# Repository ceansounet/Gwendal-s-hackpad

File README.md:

# Gwendal-s-hackpad
My personnal Hackpad

## PCB
here is the schematic of my pcb :

and here is the resulting layout, it needs to be pretty compact to fit in the 100mm*100mm requirements

The silkscreen was made on figma and imported as an SVG. (sources are [here](pcb/assets))

## BONUS
Since I had extra space and the kit comes with them, I figured I could include the rotary encoders inside a bonus version of my hackpad, while the main version keeps only 16 inputs to fit within the limit

## BOM:
Here should be everything you need to make this hackpad

in the kit :
- 16x Cherry MX Switches
- 16x DSA Keycaps
- 2x M3x5x4 Heatset inserts
- 2X M3x12mm SHCS Bolts
- 16x 1N4148 DO-35 Diodes
- 1x 0.91" 128x32 OLED Display
- 1x XIAO RP2040
- 1x Case (3 printed parts)

to source yourself :
- 1x MCP23017 (I²C IO expander)
- 1x 100nF Capacitor (decoupling the MCP power)
- 8x 4.7k ohm resistors (pull up/pull down resistors for the matrix and the I²C circuit)

Optional :
- 2x EC11 Rotary Encoder
- 2x 1N4148 DO-35 Diodes
- 1x 8cm² cork sheet (for the bottom of the case)

## EXTRA STUFF :
I designed this project in 4 days of vacation, learnt to use kicad and pcb design in general
If firmware doesn't support 2 different I²C circuits, I added 0 ohm resistors (R9 and R10), that can be soldered shut to make a single I²C circuit, currently it uses 2 by default for speed and stability.
I designed the case to be 3d printable without supports (exept the cutout bit on the top cover, purely for aesthetic purposes, feel free to fill it in to avoid supports entirely).
I made some firmware that should support the matrix, but does not support the encoders nor the OLED screen yet, I am waiting until I have actually made the board to test it.

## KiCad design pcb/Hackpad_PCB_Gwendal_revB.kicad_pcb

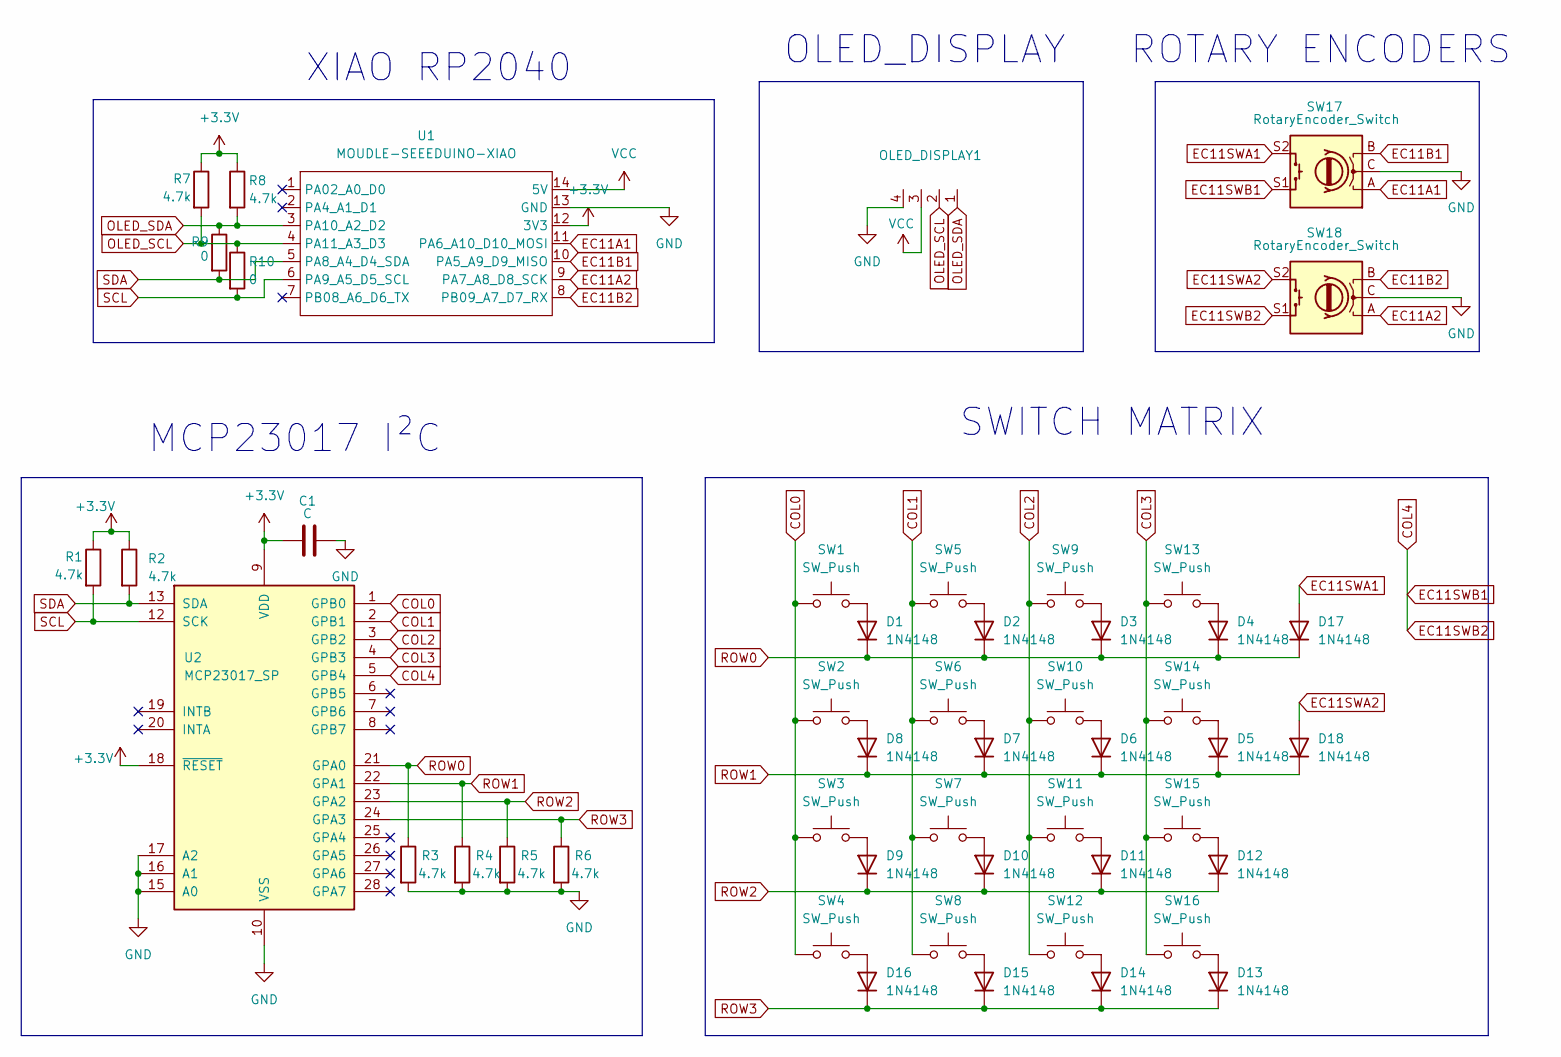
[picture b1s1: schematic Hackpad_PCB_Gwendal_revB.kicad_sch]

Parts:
C1: C; C_Disc_D5.0mm_W2.5mm_P5.00mm
D1, D2, D3, D4, D5, D6, D7, D8, D9, D10, D11, D12, D13, D14, D15, D16, D17, D18: 1N4148; D_DO-35_SOD27_P7.62mm_Horizontal
OLED_DISPLAY1: PinHeader_1x04_P2.54mm_Vertical
R1, R2, R3, R4, R5, R6, R7, R8: 4.7k; R_Axial_DIN0207_L6.3mm_D2.5mm_P7.62mm_Horizontal
R9, R10: 0; R_Axial_DIN0207_L6.3mm_D2.5mm_P7.62mm_Horizontal
SW1, SW2, SW3, SW4, SW5, SW6, SW7, SW8, SW9, SW10, SW11, SW12, SW13, SW14, SW15, SW16: SW_Push; SW_Cherry_MX_1.00u_PCB
SW17, SW18: RotaryEncoder_Switch; RotaryEncoder_Alps_EC11E-Switch_Vertical_H20mm
U1: MOUDLE-SEEEDUINO-XIAO; XIAO-Generic-Hybrid-14P-2.54-21X17.8MM
U2: MCP23017_SP; DIP-28_W7.62mm

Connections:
+3.3V: C1.1, R1.1, R2.1, R7.1, R8.1, U1.12 (3V3), U2.9 (VDD), U2.18 (~RESET)
COL0: SW1.1, SW2.1, SW3.1, SW4.1, U2.1 (GPB0)
COL1: SW5.1, SW6.1, SW7.1, SW8.1, U2.2 (GPB1)
COL2: SW9.1, SW10.1, SW11.1, SW12.1, U2.3 (GPB2)
COL3: SW13.1, SW14.1, SW15.1, SW16.1, U2.4 (GPB3)
COL4: SW17.S1, SW18.S1, U2.5 (GPB4)
EC11A1: SW17.A, U1.11 (PA6_A10_D10_MOSI)
EC11A2: SW18.A, U1.9 (PA7_A8_D8_SCK)
EC11B1: SW17.B, U1.10 (PA5_A9_D9_MISO)
EC11B2: SW18.B, U1.8 (PB09_A7_D7_RX)
EC11SWA1: D17.2 (A), SW17.S2
EC11SWA2: D18.2 (A), SW18.S2
GND: C1.2, OLED_DISPLAY1.4, R3.2, R4.2, R5.2, R6.2, SW17.C, SW18.C, U1.13 (GND), U2.10 (VSS), U2.15 (A0), U2.16 (A1), U2.17 (A2)
unnamed: D1.2 (A), SW1.2
unnamed: D2.2 (A), SW5.2
unnamed: D3.2 (A), SW9.2
unnamed: D4.2 (A), SW13.2
unnamed: D5.2 (A), SW14.2
unnamed: D6.2 (A), SW10.2
unnamed: D7.2 (A), SW6.2
unnamed: D8.2 (A), SW2.2
unnamed: D9.2 (A), SW3.2
unnamed: D10.2 (A), SW7.2
unnamed: D11.2 (A), SW11.2
unnamed: D12.2 (A), SW15.2
unnamed: D13.2 (A), SW16.2
unnamed: D14.2 (A), SW12.2
unnamed: D15.2 (A), SW8.2
unnamed: D16.2 (A), SW4.2
OLED_SCL: OLED_DISPLAY1.2, R7.2, R10.1, U1.4 (PA11_A3_D3)
OLED_SDA: OLED_DISPLAY1.1, R8.2, R9.1, U1.3 (PA10_A2_D2)
ROW0: D1.1 (K), D2.1 (K), D3.1 (K), D4.1 (K), D17.1 (K), R3.1, U2.21 (GPA0)
ROW1: D5.1 (K), D6.1 (K), D7.1 (K), D8.1 (K), D18.1 (K), R4.1, U2.22 (GPA1)
ROW2: D9.1 (K), D10.1 (K), D11.1 (K), D12.1 (K), R5.1, U2.23 (GPA2)
ROW3: D13.1 (K), D14.1 (K), D15.1 (K), D16.1 (K), R6.1, U2.24 (GPA3)
SCL: R1.2, R10.2, U1.6 (PA9_A5_D5_SCL), U2.12 (SCK)
SDA: R2.2, R9.2, U1.5 (PA8_A4_D4_SDA), U2.13 (SDA)
VCC: OLED_DISPLAY1.3, U1.14 (5V)

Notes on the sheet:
XIAO RP2040
MCP23017 I²C
ROTARY ENCODERS
OLED_DISPLAY
SWITCH MATRIX

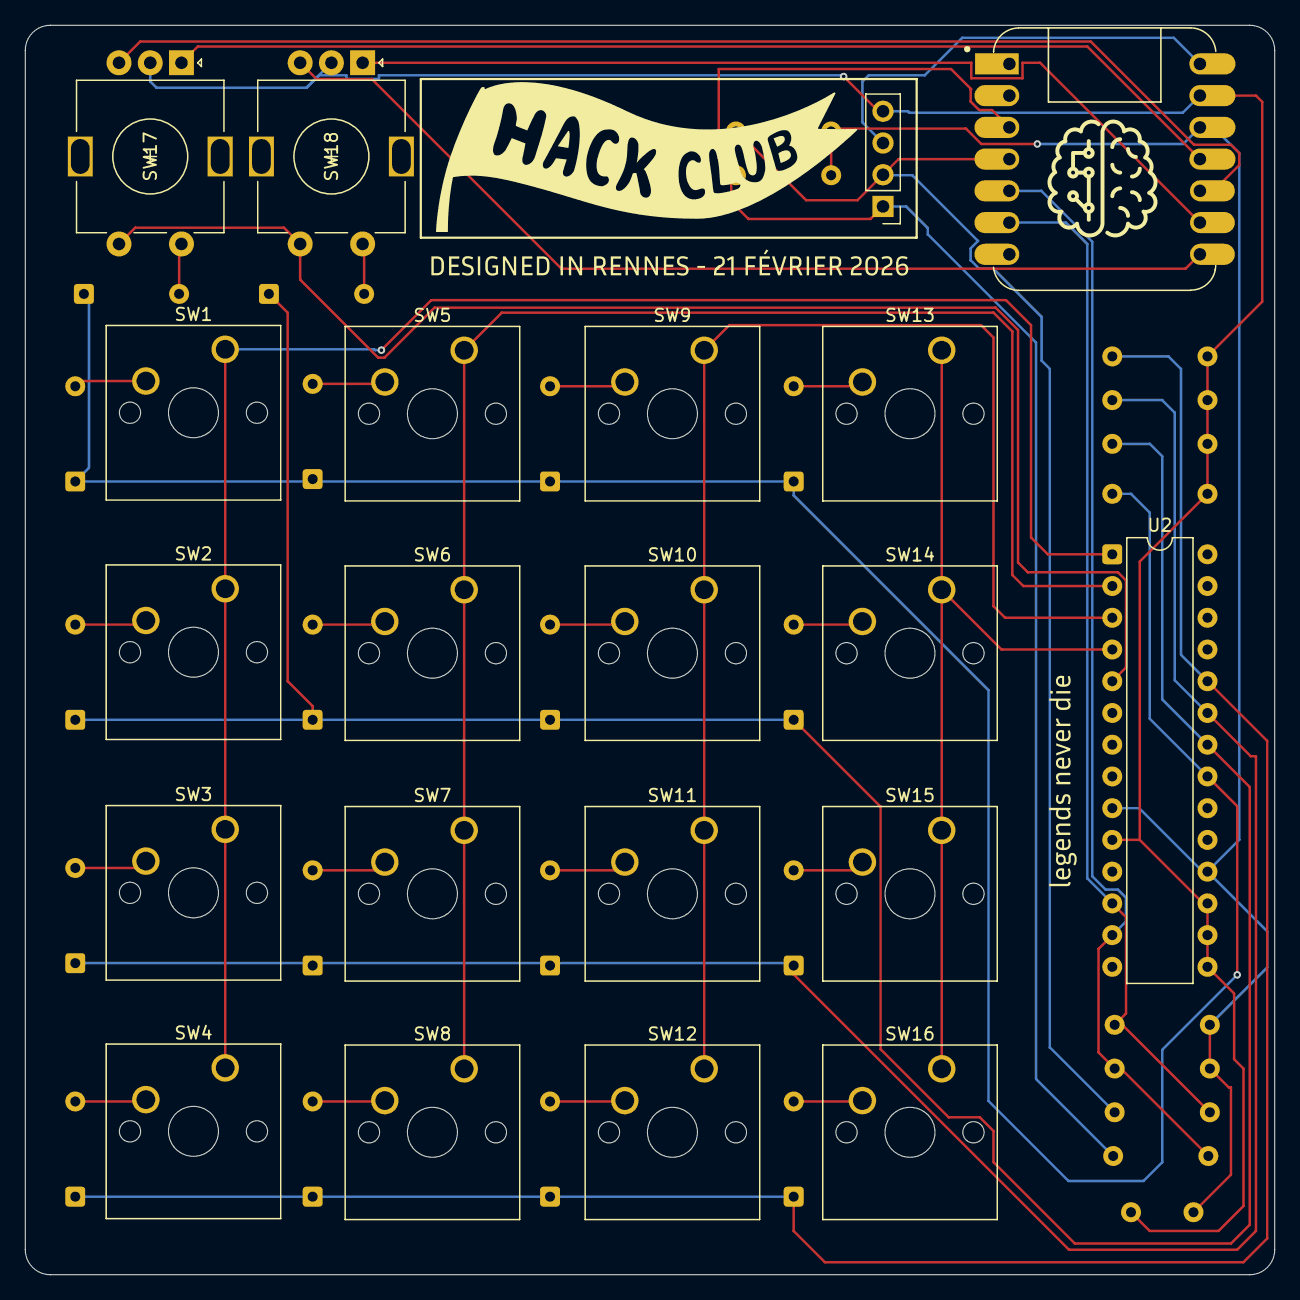
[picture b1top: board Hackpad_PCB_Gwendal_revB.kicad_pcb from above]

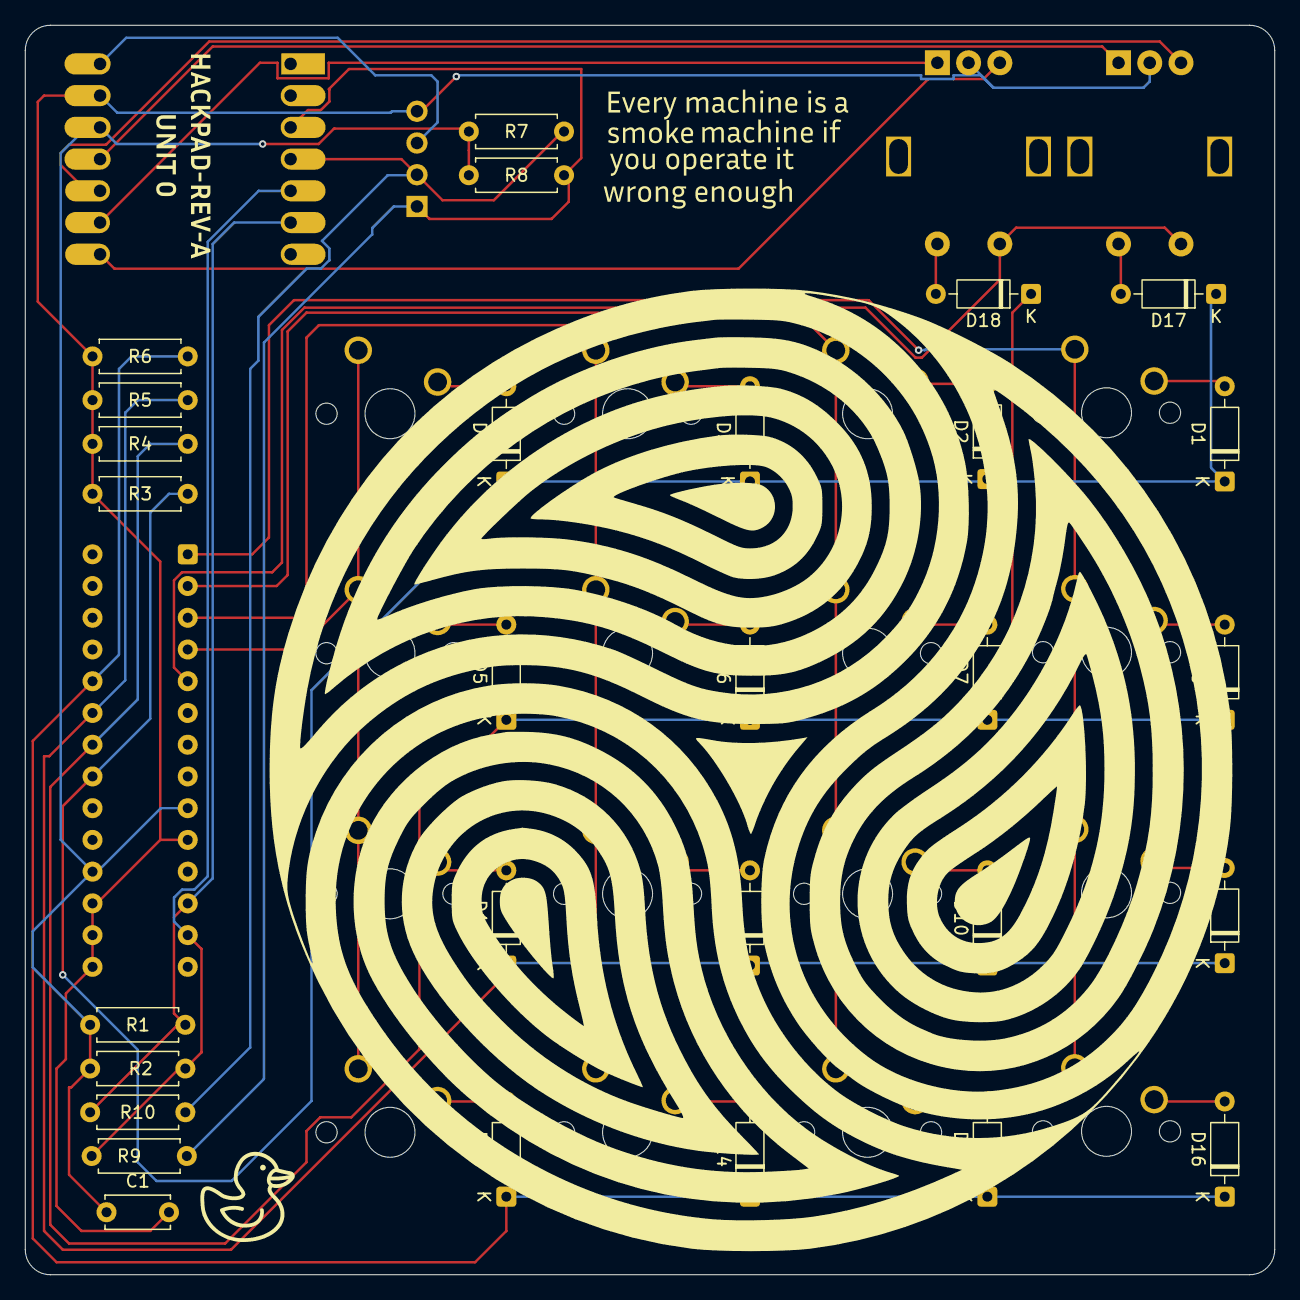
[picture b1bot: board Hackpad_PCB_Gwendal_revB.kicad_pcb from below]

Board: 2 copper layers, 100.0 x 100.0 mm, 50 parts (29 on the bottom side), 38 nets.

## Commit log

2026-02-23 SEEEENNNDDD IIITTTTTT
2026-02-23 Rename Top_cover_without_rotary_encoders.stl to Top_cover_main
2026-02-23 Rename Top_cover_with_rotary_encoders.stl to Top_cover_BONUS_(with_rotary_encoders).stl
2026-02-25 replaced firmware placeholders with actual compiled firmware (untested, lacking a lot of features)
2026-02-25 Edited Oled pullups to be 3.3v reference instead of 5v, I won't edit all of the pictures for such a small change.
2026-02-25 Updated the pictures to show to switch from logic level 5v to 3.3v on the I2C circuit for the oled screen.
2026-02-25 Update README.md
    just wanted to refresh the pictures
2026-02-26 Added cad and code source files.
2026-03-01 Added a copper fill zone to the front and back of the PCB.
2026-03-07 Updated "MADE IN RENNES" to "DESIGNED IN RENNES" on the pcb graphics, as JLCPCB failed the first audit because of it.
2026-03-22 Updated firmware, now every key works, still missing the OLED screen and the rotary encoder support
2026-04-05 -added some material so that the top cover would print without supports -added chamfers to the heat set insert holes, and made them deeper -added a flexible tab at the back of the top cover to make i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
